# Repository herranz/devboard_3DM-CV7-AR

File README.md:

<div align="center">

  <h1> DevBoard 3DM-CV7-AR </h1>
  <p> DevBoard for the Parker 3DM-CV7-AR IMU </p>

<!-- Badges -->

<h4>
    <a href="https://bsky.app/profile/herranz.bsky.social">BLUESKY</a>
  <span> · </span>
    <a href="https://www.github.com/herranz">GITHUB</a>
  
  </h4>

</div>

<br />

<div>&nbsp;</div>

## Table of Contents
* [General Info](#general-information)
* [Screenshots](#screenshots)
* [Setup](#setup)
* [Usage](#usage)
* [Project Status](#project-status)
* [Room for Improvement](#room-for-improvement)
* [Acknowledgements](#acknowledgements)
* [Contact](#contact)
* [License](#license)

## General Information
- A standalone development board for the [3DMCV7-AR](https://www.microstrain.com/inertial-sensors/3dmcv7-ar), designed for integration into robotic systems. It features dual connection options (UART or miniUSB) and includes a PCB layout optimized to minimize interference with the magnetometer. 
<!-- You don't have to answer all the questions - just the ones relevant to your project. -->

<!--
## Technologies Used
- Tech 1 - version 1.0
- Tech 2 - version 2.0
- Tech 3 - version 3.0

## Features
List the ready features here:
- Awesome feature 1
- Awesome feature 2
- Awesome feature 3

-->
## Screenshots

## Setup

The board was ordered through [JLCPCB](https://www.jlcpcb.com), utilizing their stack for controlled-impedance, JLC04161H-7628. While USB 2.0 at 12 Mbps is forgiving, it's best to adhere to the specifications for optimal performance.

If you're looking to save time, you can skip the UART LED indicators without impacting core functionality.

## Usage
The board is self-powered when used with USB (preferred mode). If USB is not used, ensure that the Vin does not exceed 5V to remain within specifications. Voltage levels for the serial connection should be TTL.

## Project Status
Project is: __COMPLETE__ 

## Room for Improvement

Room for improvement:
- Fix Silkscreen nomenclature for the Rs and Us in the UART led indicators

## Acknowledgements
- Thanks to caffeine, my soldering iron, and gravity for keeping this project (mostly) grounded. 

## Contact
Created by [@herranz]- feel free to contact me!

 ## License 
 This project is open source and available under the **CERN-OHL-S-2.0 license**

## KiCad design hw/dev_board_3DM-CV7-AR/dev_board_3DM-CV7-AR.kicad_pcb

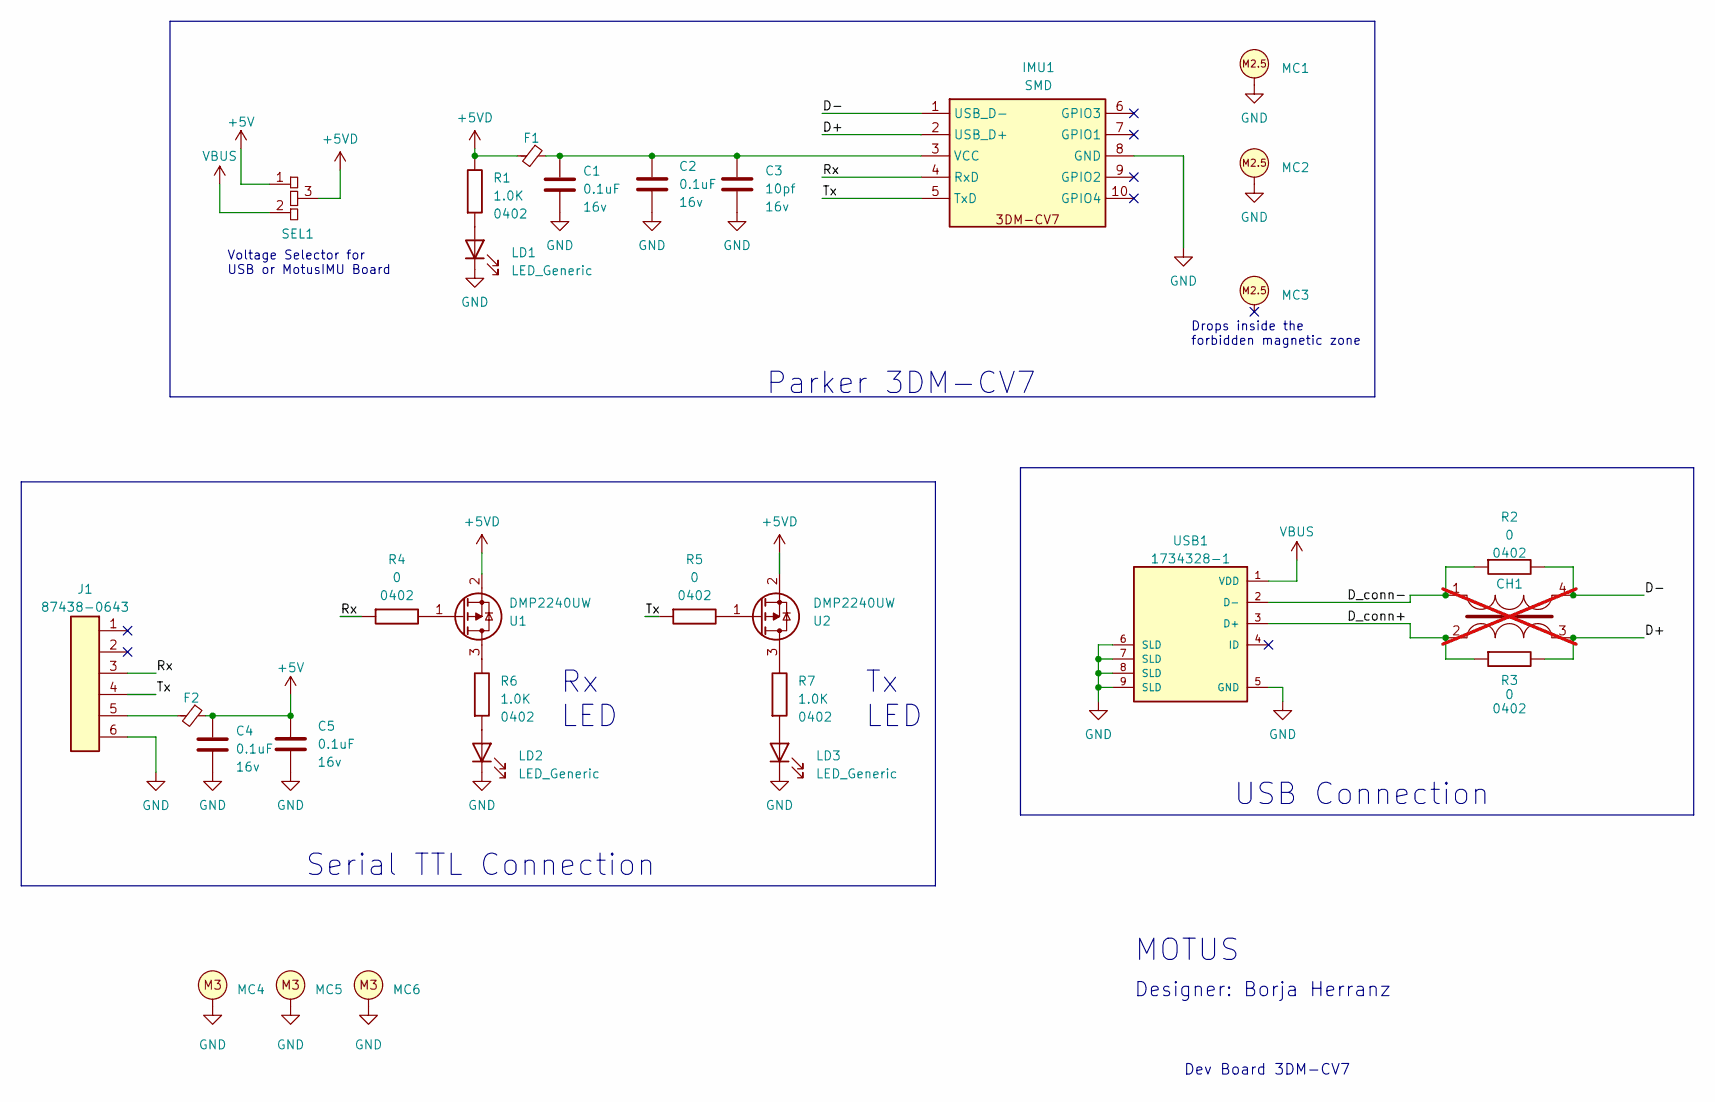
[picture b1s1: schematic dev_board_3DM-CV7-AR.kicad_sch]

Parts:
C1, C4: 0.1uF; C_0805_2012Metric; Voltage 16v
C2, C5: 0.1uF; C_0402_1005Metric; Voltage 16v
C3: 10pf; C_0402_1005Metric; Voltage 16v
CH1: XFMR_CM0805D900R-10; not fitted
F1, F2: L_0402_1005Metric_Pad0.77x0.64mm_HandSolder
IMU1: SMD; 3DM-CV7
J1: 87438-0643; Molex_picoSPOX_87438-3.5A_1x6_P1.5mm_Horizontal; MPN 87438-0643
LD1, LD2, LD3: LED_Generic; LED_0402_1005Metric_Pad0.77x0.64mm_HandSolder
MC1, MC2, MC3: M2.5_2mm_Insert; SMTSOB-M25-2ET
MC4, MC5, MC6: M3_Hole
R1, R6, R7: 1.0K; R_0402_1005Metric
R2, R3, R4, R5: 0; R_0402_1005Metric
SEL1: pad_selector
U1, U2: DMP2240UW; SOT-323_SC-70
USB1: 1734328-1; TE_1734328-1

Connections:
+5V: C4.1, C5.1, F2.2, SEL1.1
+5VD: F1.1, R1.2, SEL1.3, U1.2 (S), U2.2 (S)
/D+: CH1.3, IMU1.2 (USB_D+), R3.2
/D-: CH1.4, IMU1.1 (USB_D-), R2.2
/D_conn+: CH1.2, R3.1, USB1.3 (D+)
/D_conn-: CH1.1, R2.1, USB1.2 (D-)
/Rx: IMU1.4 (RxD), J1.3, R4.1
/Tx: IMU1.5 (TxD), J1.4, R5.1
GND: C1.2, C2.2, C3.2, C4.2, C5.2, IMU1.8 (GND), J1.6, LD1.2 (K), LD2.2 (K), LD3.2 (K), MC1.1, MC2.1, MC4.1, MC5.1, MC6.1, USB1.5 (GND), USB1.6 (SLD), USB1.7 (SLD), USB1.8 (SLD), USB1.9 (SLD)
unnamed: C1.1, C2.1, C3.1, F1.2, IMU1.3 (VCC)
unnamed: F2.1, J1.5
unnamed: LD1.1 (A), R1.1
unnamed: LD2.1 (A), R6.1
unnamed: LD3.1 (A), R7.1
unnamed: R6.2, U1.3 (D)
unnamed: R4.2, U1.1 (G)
unnamed: R7.2, U2.3 (D)
unnamed: R5.2, U2.1 (G)
VBUS: SEL1.2, USB1.1 (VDD)

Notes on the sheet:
USB Connection
Serial TTL Connection
Designer: Borja Herranz
Drops inside the forbidden magnetic zone
Parker 3DM-CV7
MOTUS
Dev Board 3DM-CV7
Tx LED
Rx LED
Voltage Selector for USB or MotusIMU Board

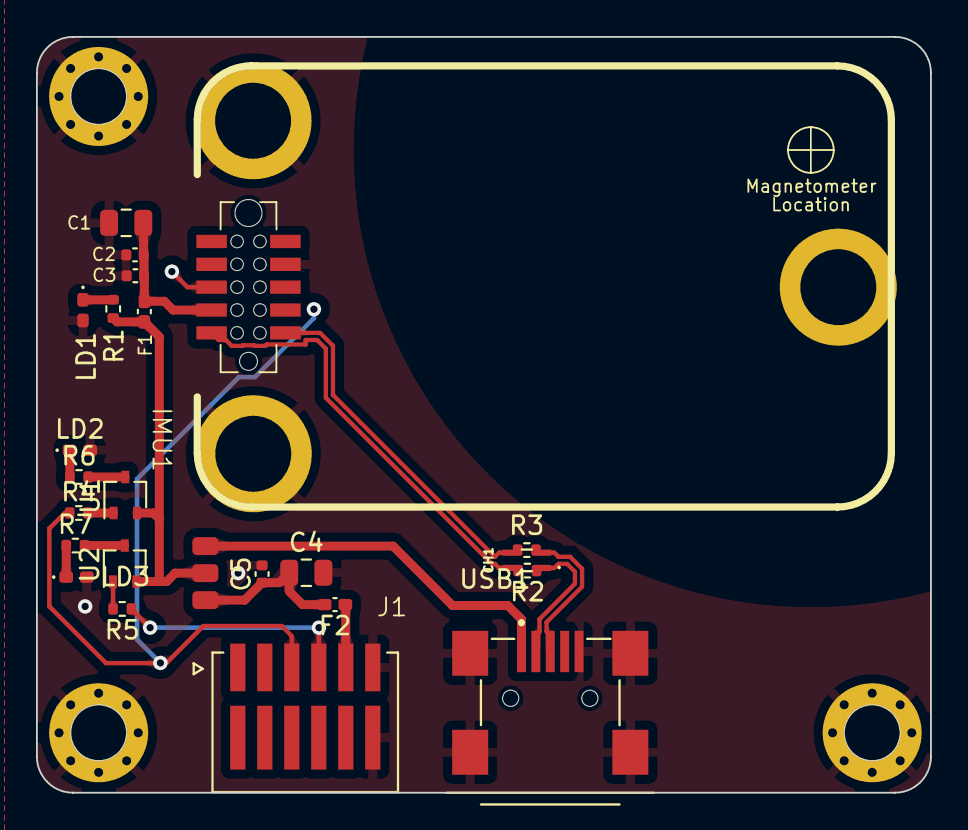
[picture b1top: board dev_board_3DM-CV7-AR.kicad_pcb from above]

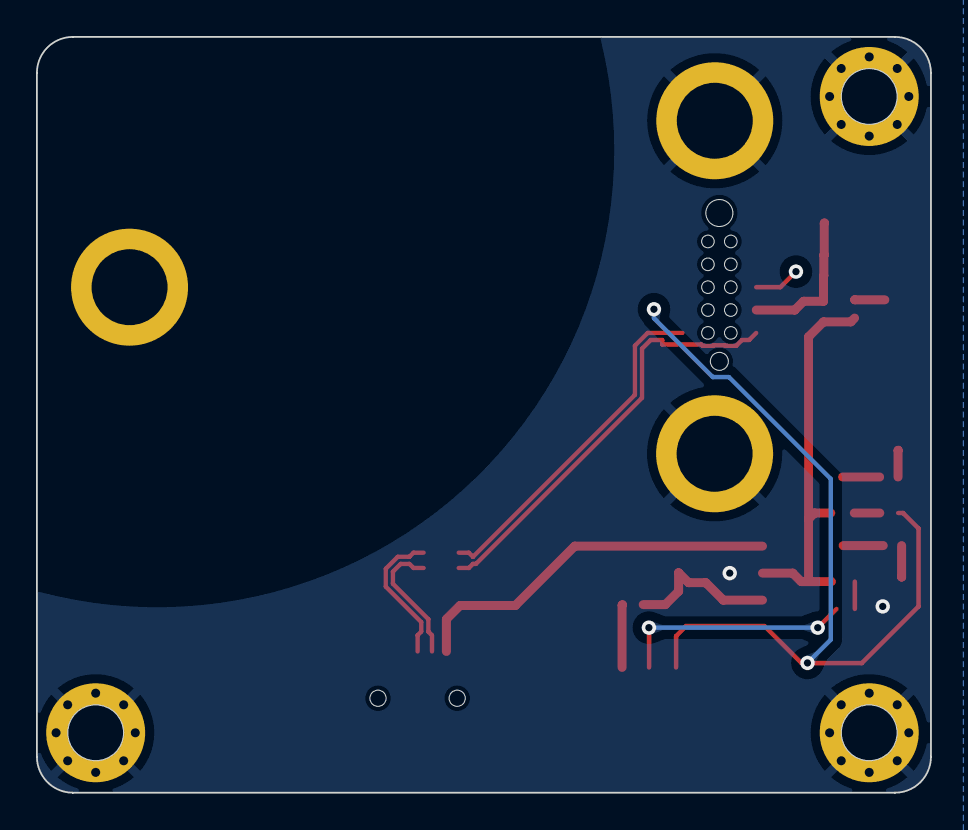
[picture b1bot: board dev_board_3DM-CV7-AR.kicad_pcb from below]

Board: 4 copper layers, 49.7 x 42.0 mm, 30 parts (3 on the bottom side), 19 nets.

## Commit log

2023-11-07 First commit. Added IMU, USB and filters
2023-11-08 Añadido CM Choke
2023-11-10 Añadido Leds TX-RX
2023-11-13 arreglado linea diferencial
2023-11-14 Finalizado
2024-12-19 Update README.md
    Updated the readme for CV
2024-12-19 Update for public release
